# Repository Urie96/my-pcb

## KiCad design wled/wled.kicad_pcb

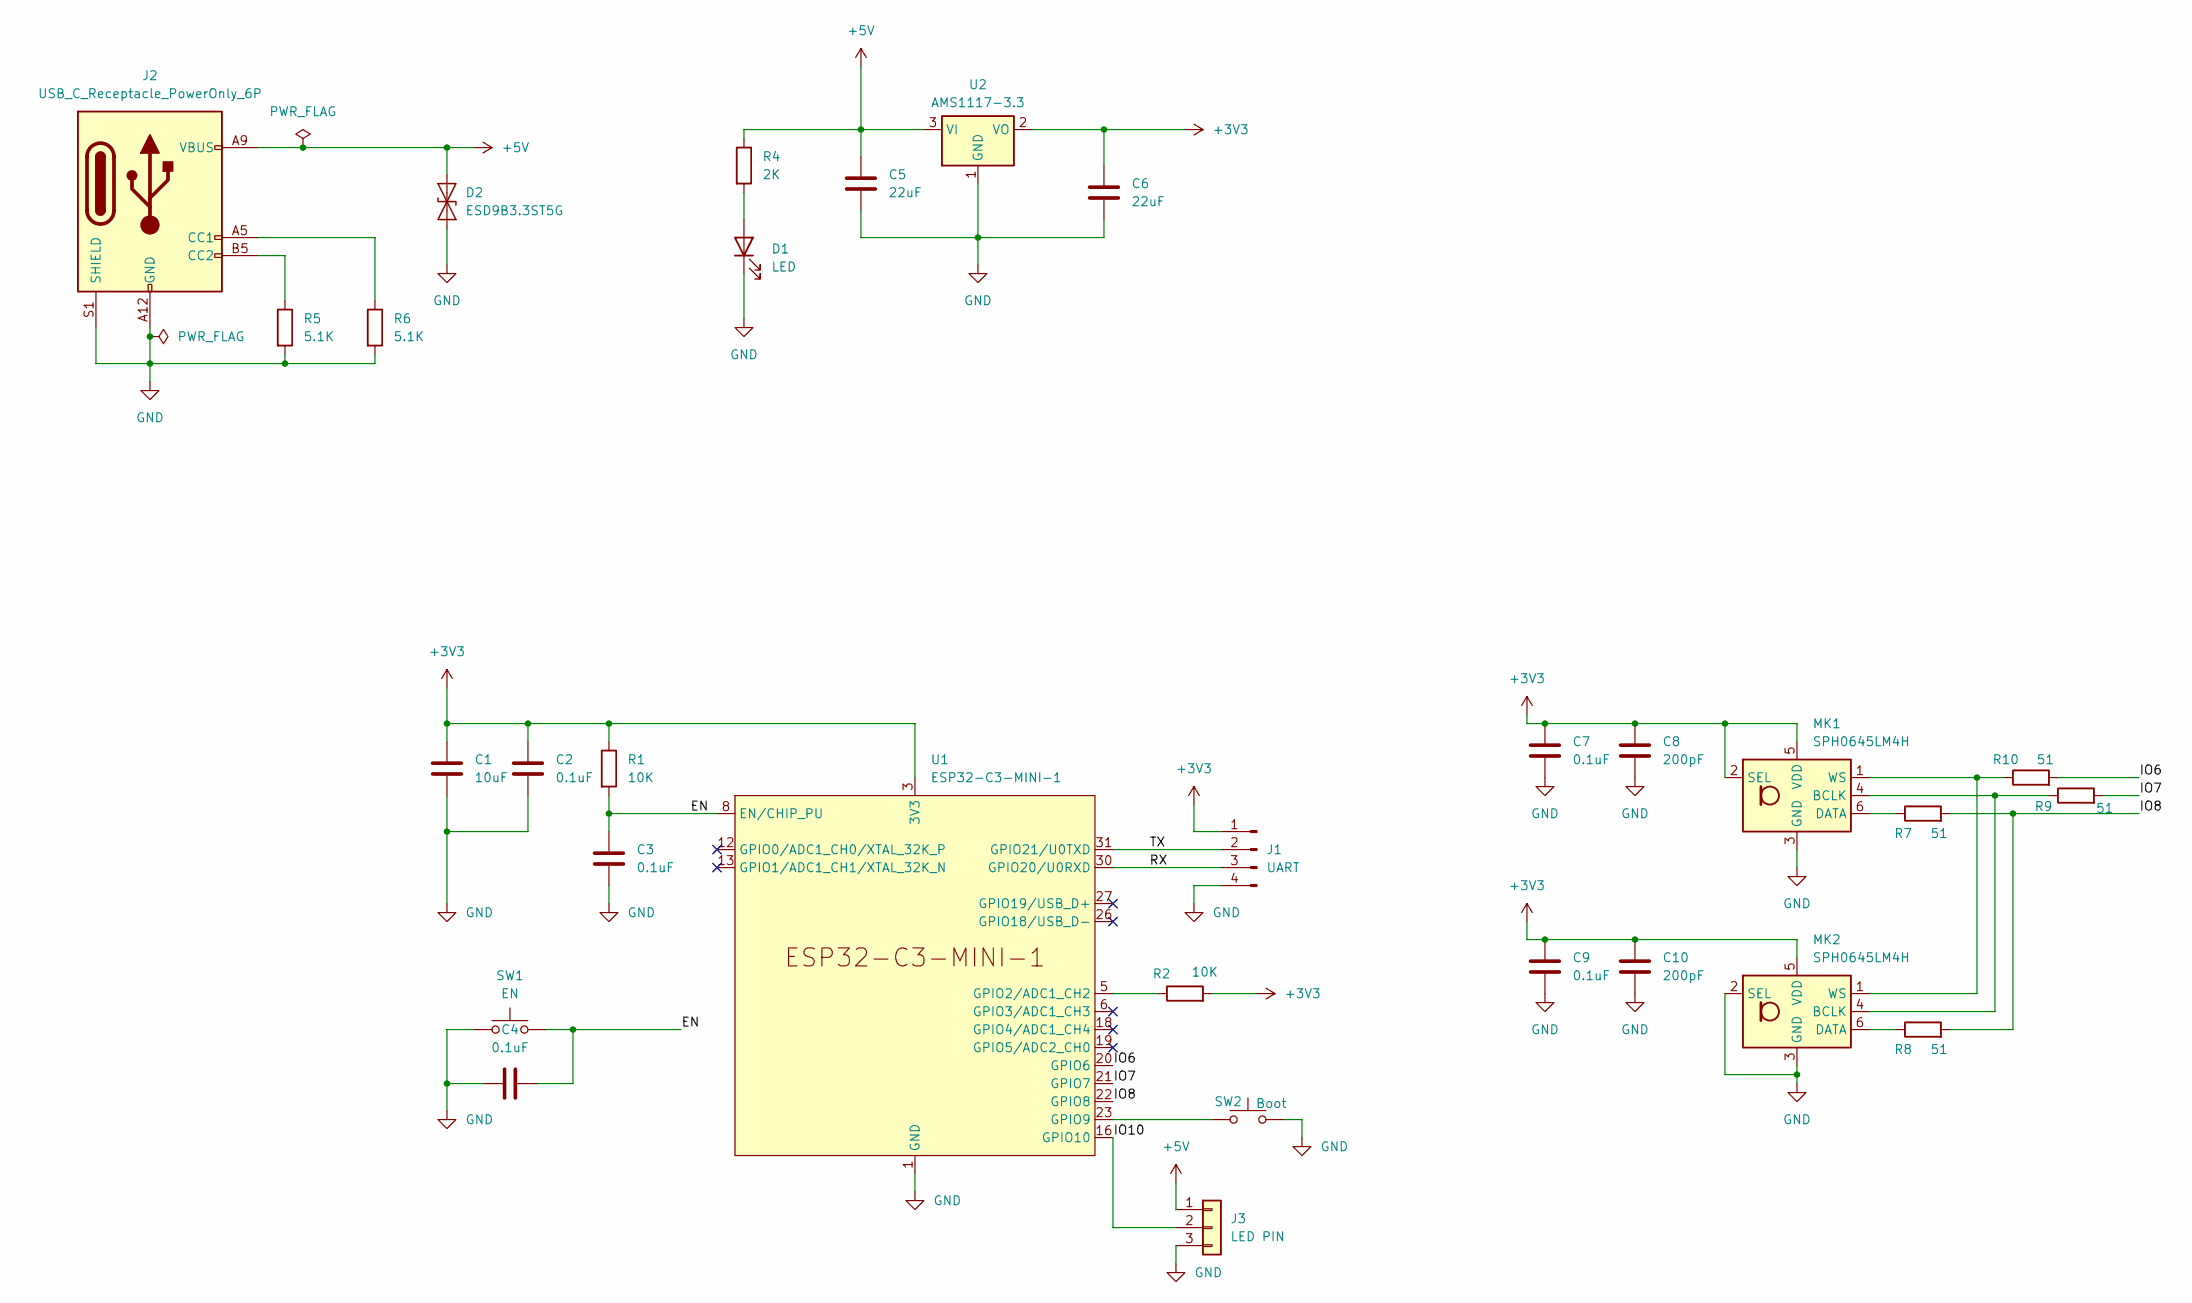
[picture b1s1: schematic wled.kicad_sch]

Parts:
C1: 10uF; C_0805_2012Metric
C2, C3, C4, C7, C9: 0.1uF; C_0805_2012Metric
C5, C6: 22uF; C_0805_2012Metric
C8, C10: 200pF; C_0805_2012Metric
D1: LED; LED_0805_2012Metric
D2: ESD9B3.3ST5G; D_0805_2012Metric
J1: UART; PinHeader_1x04_P2.54mm_Vertical
J2: USB_C_Receptacle_PowerOnly_6P; USB_C_Receptacle_GCT_USB4125-xx-x-0190_6P_TopMnt_Horizontal
J3: LED PIN; PinHeader_1x03_P2.54mm_Horizontal
MK1, MK2: SPH0645LM4H; Knowles_SPH0645LM4H-6_3.5x2.65mm
R1, R2: 10K; R_0805_2012Metric
R4: 2K; R_0805_2012Metric
R5, R6: 5.1K; R_0805_2012Metric
R7, R8, R9, R10: 51; R_0805_2012Metric
SW1: EN; SW_Push_SPST_NO_Alps_SKRK
SW2: Boot; SW_Push_SPST_NO_Alps_SKRK
U1: ESP32-C3-MINI-1
U2: AMS1117-3.3; SOT-223-3_TabPin2

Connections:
+3V3: C1.1, C2.1, C6.1, C7.1, C8.1, C9.1, C10.1, J1.1, MK1.2 (SEL), MK1.5 (VDD), MK2.5 (VDD), R1.1, R2.2, U1.3 (3V3), U2.2 (VO)
+5V: C5.1, D2.2 (A2), J2.A9 (VBUS), J2.B9 (VBUS), J3.1, R4.1, U2.3 (VI)
/EN: C3.1, C4.2, R1.2, SW1.2, U1.8 (EN/CHIP_PU)
/IO6: R10.2, U1.20 (GPIO6)
/IO7: R9.2, U1.21 (GPIO7)
/IO8: R7.2, R8.2, U1.22 (GPIO8)
/IO10: J3.2, U1.16 (GPIO10)
/RX: J1.3, U1.30 (GPIO20/U0RXD)
/TX: J1.2, U1.31 (GPIO21/U0TXD)
GND: C1.2, C2.2, C3.2, C4.1, C5.2, C6.2, C7.2, C8.2, C9.2, C10.2, D1.1 (K), D2.1 (A1), J1.4, J2.A12 (GND), J2.B12 (GND), J2.S1 (SHIELD), J3.3, MK1.3 (GND), MK2.2 (SEL), MK2.3 (GND), R5.2, R6.2, SW1.1, SW2.2, U1.1 (GND), U1.2 (GND), U1.11 (GND), U1.14 (GND), U1.36 (GND), U1.37 (GND), U1.38 (GND), U1.39 (GND), U1.40 (GND), U1.41 (GND), U1.42 (GND), U1.43 (GND), U1.44 (GND), U1.45 (GND), U1.46 (GND), U1.47 (GND), U1.48 (GND), U1.49 (GND), U1.50 (GND), U1.51 (GND), U1.52 (GND), U1.53 (GND), U2.1 (GND)
unnamed: D1.2 (A), R4.2
unnamed: J2.A5 (CC1), R6.1
unnamed: J2.B5 (CC2), R5.1
unnamed: MK1.4 (BCLK), MK2.4 (BCLK), R9.1
unnamed: MK1.6 (DATA), R7.1
unnamed: MK1.1 (WS), MK2.1 (WS), R10.1
unnamed: MK2.6 (DATA), R8.1
unnamed: R2.1, U1.5 (GPIO2/ADC1_CH2)
unnamed: SW2.1, U1.23 (GPIO9)

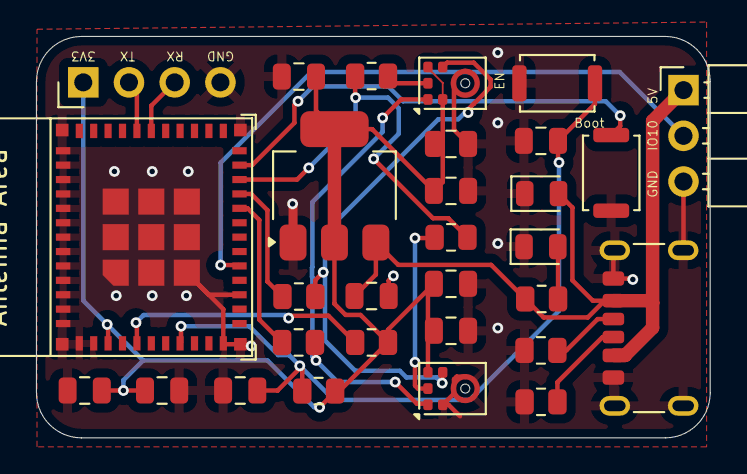
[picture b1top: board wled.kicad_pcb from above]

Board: 2 copper layers, 37.4 x 22.3 mm, 30 parts (0 on the bottom side), 19 nets.

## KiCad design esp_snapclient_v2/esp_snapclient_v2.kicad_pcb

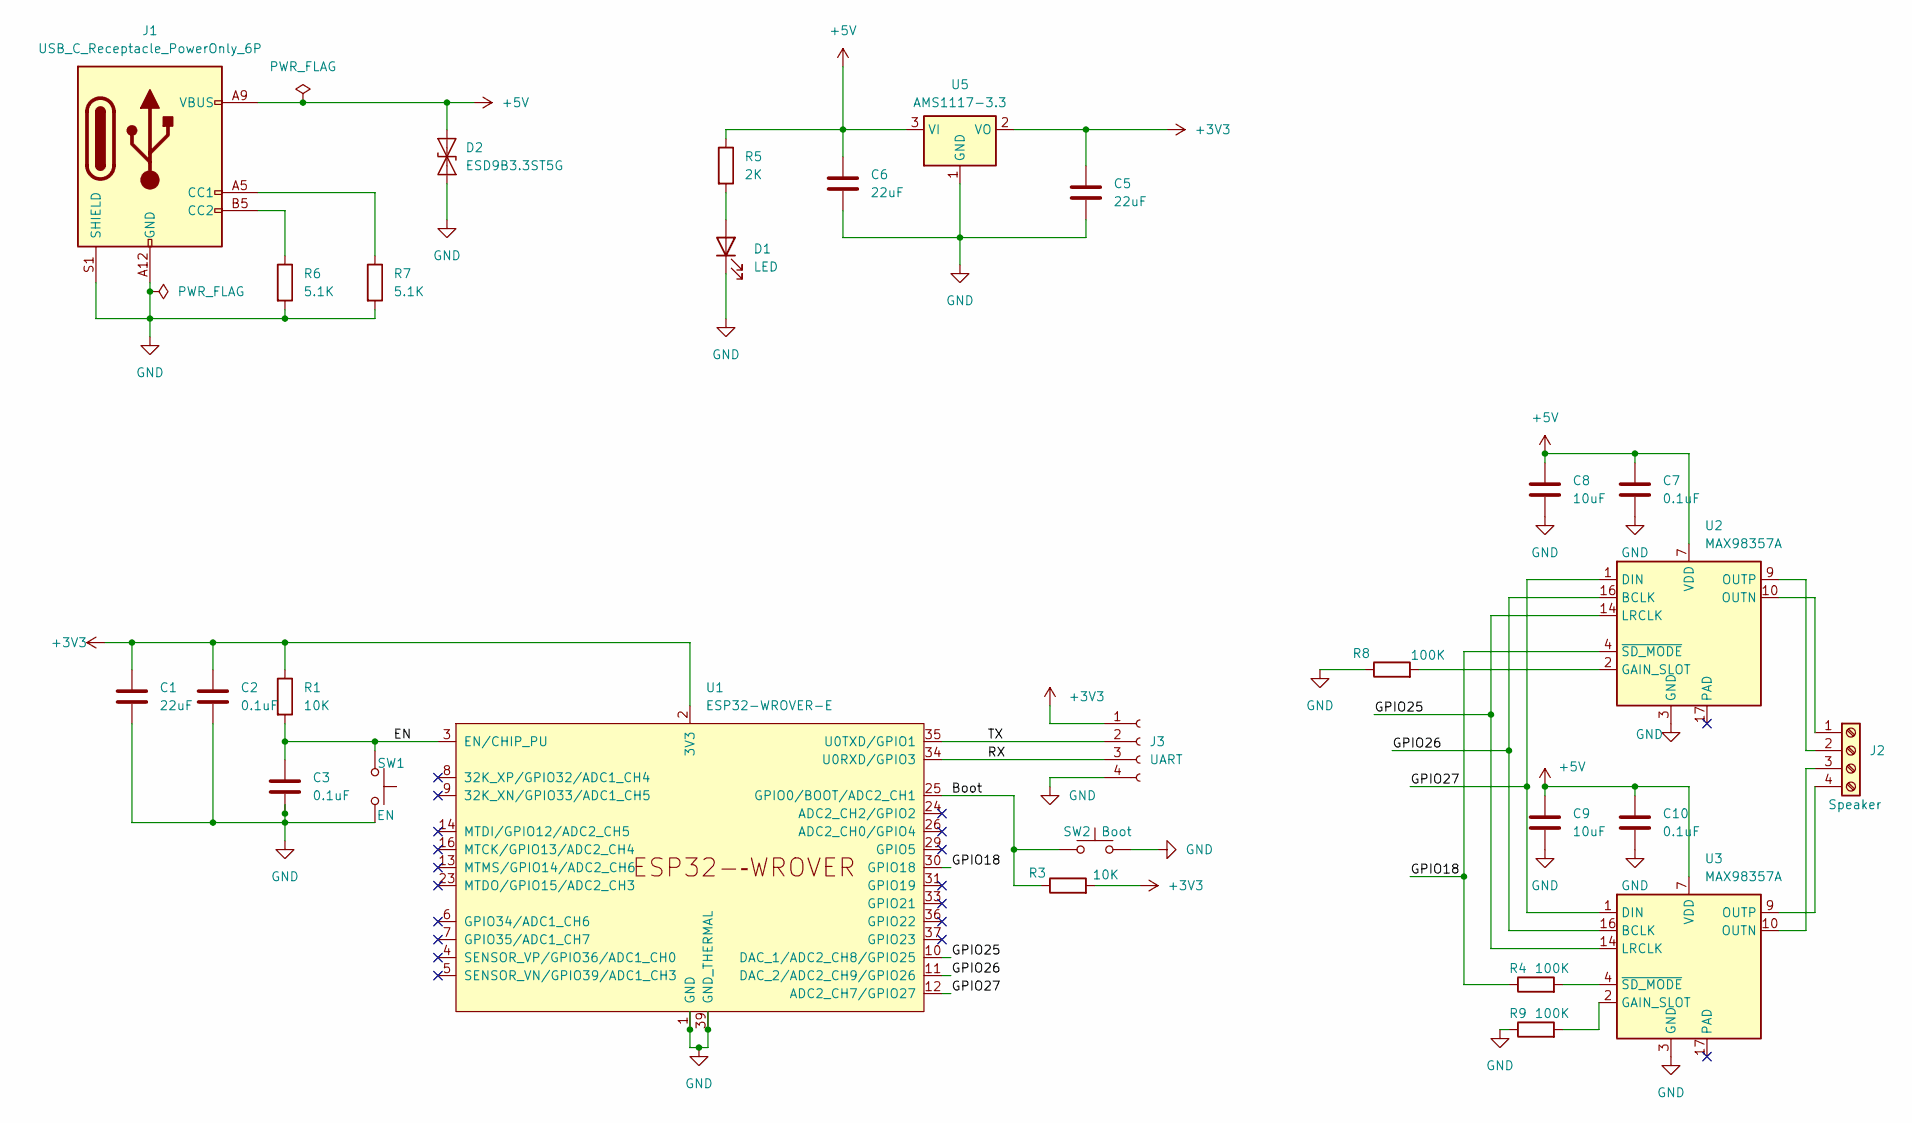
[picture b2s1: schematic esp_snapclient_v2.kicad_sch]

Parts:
C1, C5, C6: 22uF; C_0805_2012Metric
C2, C3, C7, C10: 0.1uF; C_0805_2012Metric
C8, C9: 10uF; C_0805_2012Metric
D1: LED; LED_0805_2012Metric
D2: ESD9B3.3ST5G; D_0805_2012Metric
J1: USB_C_Receptacle_PowerOnly_6P; USB_C_Receptacle_GCT_USB4125-xx-x-0190_6P_TopMnt_Horizontal
J2: Speaker; TerminalBlock_MaiXu_MX126-5.0-04P_1x04_P5.00mm
J3: UART; PinHeader_1x04_P2.54mm_Vertical
R1, R3: 10K; R_0805_2012Metric
R4, R8, R9: 100K; R_0805_2012Metric
R5: 2K; R_0805_2012Metric
R6, R7: 5.1K; R_0805_2012Metric
SW1: EN; SW_SPST_TS-1088-xR020
SW2: Boot; SW_SPST_TS-1088-xR020
U1: ESP32-WROVER-E
U2, U3: MAX98357A; TQFN-16-1EP_3x3mm_P0.5mm_EP1.23x1.23mm
U5: AMS1117-3.3; SOT-223-3_TabPin2

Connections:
+3V3: C1.1, C2.1, C5.1, J3.1, R1.1, R3.2, U1.2 (3V3), U5.2 (VO)
+5V: C6.1, C7.1, C8.1, C9.1, C10.1, D2.2 (A2), J1.A9 (VBUS), J1.B9 (VBUS), R5.1, U2.7 (VDD), U2.8 (VDD), U3.7 (VDD), U3.8 (VDD), U5.3 (VI)
/Boot: R3.1, SW2.1, U1.25 (GPIO0/BOOT/ADC2_CH1)
/EN: C3.1, R1.2, SW1.1, U1.3 (EN/CHIP_PU)
/GPIO18: R4.1, U1.30 (GPIO18), U2.4 (~SD_MODE)
/GPIO25: U1.10 (DAC_1/ADC2_CH8/GPIO25), U2.14 (LRCLK), U3.14 (LRCLK)
/GPIO26: U1.11 (DAC_2/ADC2_CH9/GPIO26), U2.16 (BCLK), U3.16 (BCLK)
/GPIO27: U1.12 (ADC2_CH7/GPIO27), U2.1 (DIN), U3.1 (DIN)
/RX: J3.3, U1.34 (U0RXD/GPIO3)
/TX: J3.2, U1.35 (U0TXD/GPIO1)
GND: C1.2, C2.2, C3.2, C5.2, C6.2, C7.2, C8.2, C9.2, C10.2, D1.1 (K), D2.1 (A1), J1.A12 (GND), J1.B12 (GND), J1.S1 (SHIELD), J3.4, R6.2, R7.2, R8.1, R9.1, SW1.2, SW2.2, U1.1 (GND), U1.15 (GND), U1.38 (GND), U1.39 (GND_THERMAL), U2.3 (GND), U2.11 (GND), U2.15 (GND), U3.3 (GND), U3.11 (GND), U3.15 (GND), U5.1 (GND)
unnamed: D1.2 (A), R5.2
unnamed: J1.A5 (CC1), R7.1
unnamed: J1.B5 (CC2), R6.1
unnamed: J2.1, U2.10 (OUTN)
unnamed: J2.2, U2.9 (OUTP)
unnamed: J2.3, U3.10 (OUTN)
unnamed: J2.4, U3.9 (OUTP)
unnamed: R8.2, U2.2 (GAIN_SLOT)
unnamed: R9.2, U3.2 (GAIN_SLOT)
unnamed: R4.2, U3.4 (~SD_MODE)

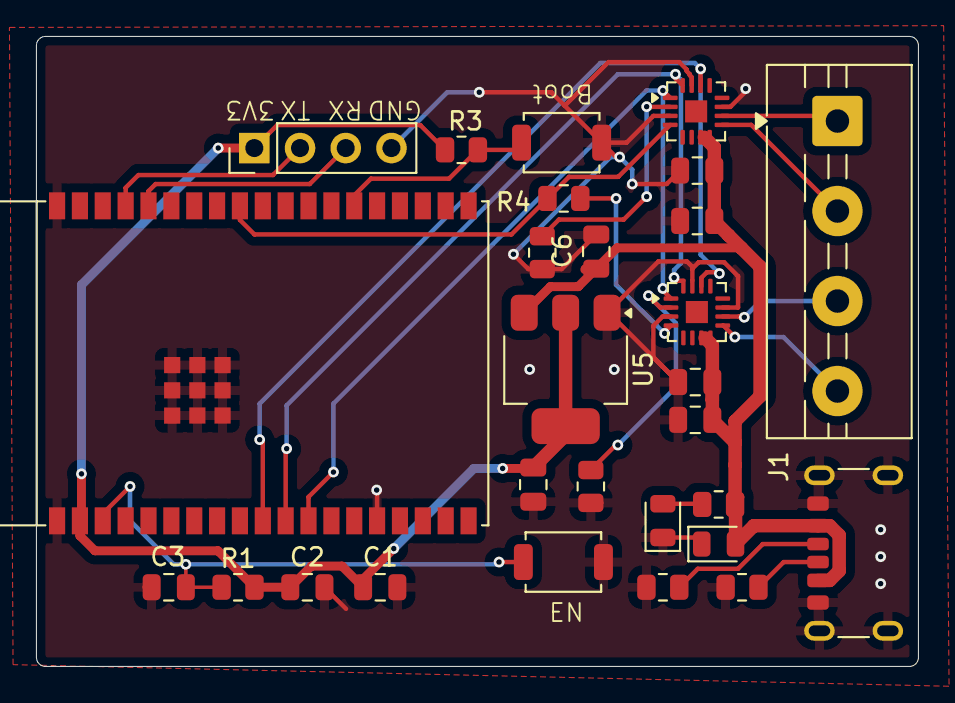
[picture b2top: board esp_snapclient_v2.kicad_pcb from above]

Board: 2 copper layers, 49.0 x 35.0 mm, 28 parts (0 on the bottom side), 21 nets.

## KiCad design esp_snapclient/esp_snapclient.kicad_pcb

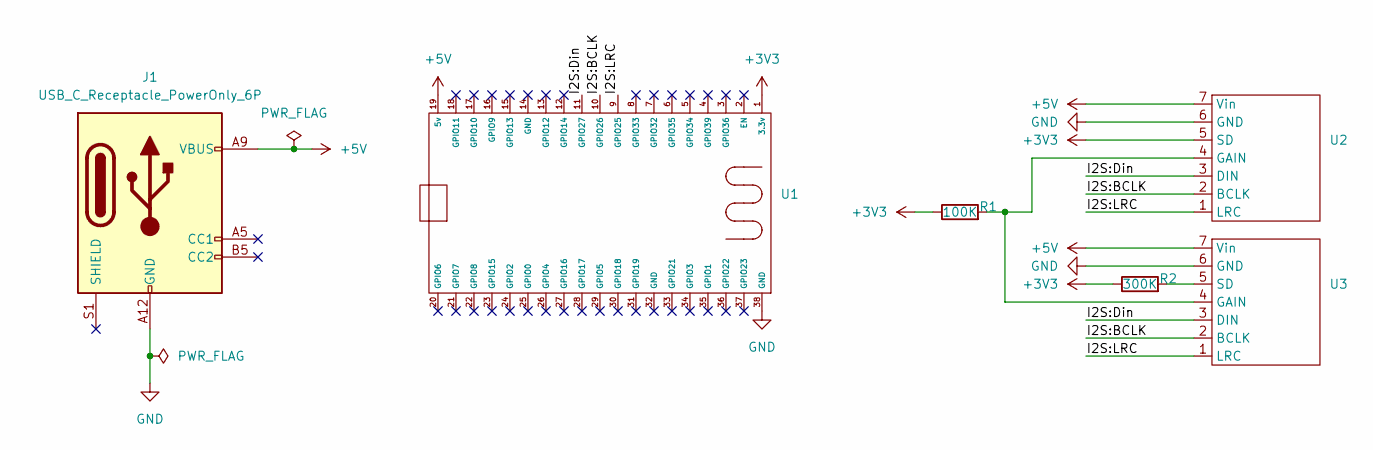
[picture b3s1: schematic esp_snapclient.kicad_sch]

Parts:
J1: USB_C_Receptacle_PowerOnly_6P; USB_C_Receptacle_GCT_USB4125-xx-x-0190_6P_TopMnt_Horizontal
R1: 100K; R_0805_2012Metric
R2: 300K; R_0805_2012Metric
U1: ESP32-DevKitC
U2, U3: max98357

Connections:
+3V3: R1.1, R2.1, U1.1 (3.3v), U2.5 (SD)
+5V: J1.A9 (VBUS), J1.B9 (VBUS), U1.19 (5v), U2.7 (Vin), U3.7 (Vin)
/I2S:BCLK: U1.10 (GPIO26), U2.2 (BCLK), U3.2 (BCLK)
/I2S:Din: U1.11 (GPIO27), U2.3 (DIN), U3.3 (DIN)
/I2S:LRC: U1.9 (GPIO25), U2.1 (LRC), U3.1 (LRC)
GND: J1.A12 (GND), J1.B12 (GND), U1.38 (GND), U2.6 (GND), U3.6 (GND)
unnamed: R1.2, U2.4 (GAIN), U3.4 (GAIN)
unnamed: R2.2, U3.5 (SD)

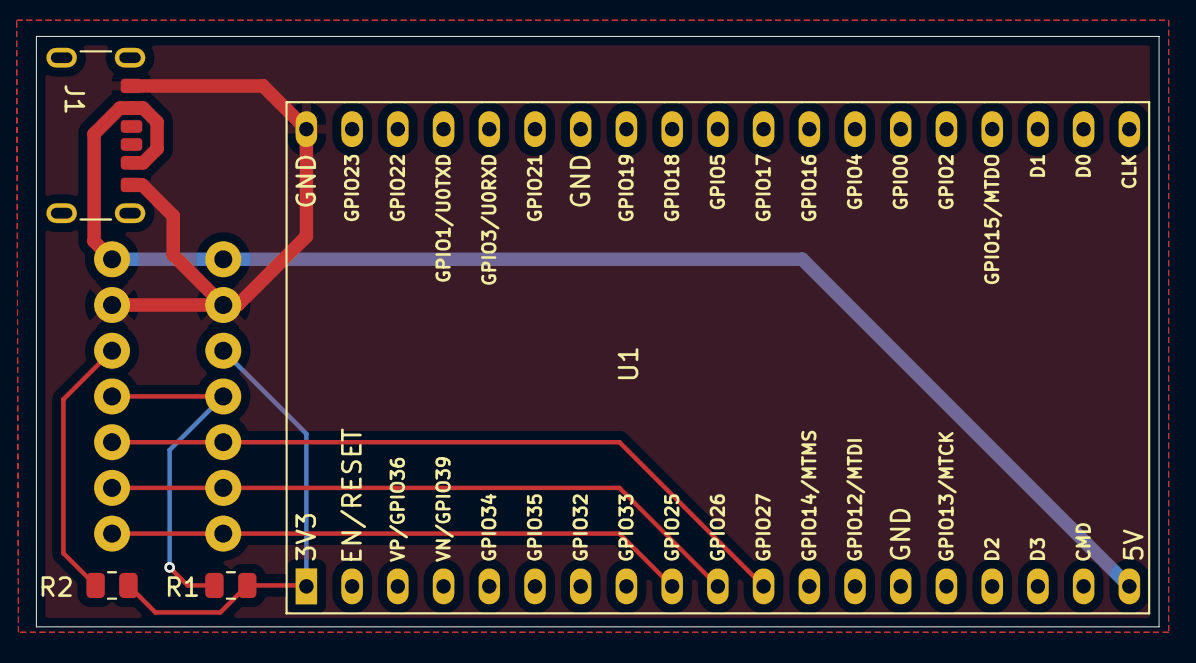
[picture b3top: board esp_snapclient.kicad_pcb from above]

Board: 2 copper layers, 62.4 x 32.8 mm, 6 parts (1 on the bottom side), 8 nets.

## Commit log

2025-12-21 feat: up
